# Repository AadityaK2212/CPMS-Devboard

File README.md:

# CPMS-Devboard

That Guy
added to the journal
DESIGN
1h logged
28d ago
Finished! :)
Did the finishing touches, and finished everything In JLCPCB

only issue is that I will need to buy some things seperately and hand soder them because JLCPCB does not have them in stock right now

That Guy
added to the journal
DESIGN
4.5h logged
30d ago
Finishing
I followed the tutorial, and finished it. It took a while, but i fixed my 63 errors, and did all the routing.

When I tried to upload to JLCPCB, the tutorial was not very helpful. I tried everything, and eventually got it through the first stsage. the the BOM. I had no idea how to do it, but after an hour, I installed a plugin, and got it. now, JLCPCB is showing me something weird in the viewer. I posted on slack, and will try to fix it tommorrow.

That Guy
added to the journal
DESIGN
1h logged
Mar 27, 2026
Routing
Nothing much, just a lot of routing, but not done with it. I did have to make a lot of things in the second layer tho.

That Guy
added to the journal
DESIGN
2.5h logged
Mar 25, 2026
Started routing the PCB
Today I started routing the PCB. the first bit went pretty smoothly, but then I started running into problems.

Some of the pins wouldn't connect, and I couldn't figure out why. I tried to figure it out on my own for 20 muinites, but couldn't figure it out. eventually, I asked on slack, and after a 15 minute discussion, I was able to fix it. then, I was able to make the rest of the Flash easily.

I then started on the USB-C. it started fine, untill I realized that two of my pins were swapped for some reason, meaning that I would have to cross the traces to rout them, which would result in a short circut. I thought I was cooked, but then I did ANOTHER 20 muinites of reasearch, and I finally figured it out. except now I had to make multiple layers on my PCB. I fixed it, but I had to move a portion of one of the traces to another layer.

All in a day's work.

That Guy
added to the journal
DESIGN
2.5h logged
Mar 24, 2026
PCB layout
I mostly just started the PCB layout. It took a while and I had to watch a few tutorials, but I got it in the end. not completely done yet though.

The memory was too large, so the tutorial swapped it out for a different version. when I tried that, it wanst in the footprint libraries, so I had to go to SnapMagic and download it. afterwards, I realized they only have the footprint, and not the schematic, so I had to create my own after some more tutorials. I finished the schematic and I am currently wiring it up. will continue on the next session.

That Guy
added to the journal
DESIGN
0.75h logged
Mar 22, 2026
Footprints
I did all the footprints today. There weren't any problems, and I got through it surprisingly easily. also changed the crystal schematic a bit.

That Guy
added to the journal
DESIGN
2.5h logged
Mar 21, 2026
Finished PCB wiring
Finished the PCB design, now I need to make the model.

I finished the USB-C with only onw issue. I didn't know how to chage the capacitors, so I posted my question on slack, and someone answered. other than tht, USB-C went fine.

I did the pinout, which was very repetitive. that alone must have taken over 20 muinites. I didn't have any issues with it.

I did the crystal with only one problem. I didn't know, but KiCad updated one of thier schematic designs, so I asked on slack and fnished it.

That Guy
added to the journal
DESIGN
1h logged
Mar 21, 2026
Starting Devboard
Watched a small tutorial, looked through the tutorial, and started the Devboard.

I started making the devboard, but ran into some minor issues because the schematic of the RP2040 is not the asme as the one in the tutorial. It has the same pins, but in a different order. hopefully won't become an issue :)

Also started on the USB-C connecter, and it's going fine so far.

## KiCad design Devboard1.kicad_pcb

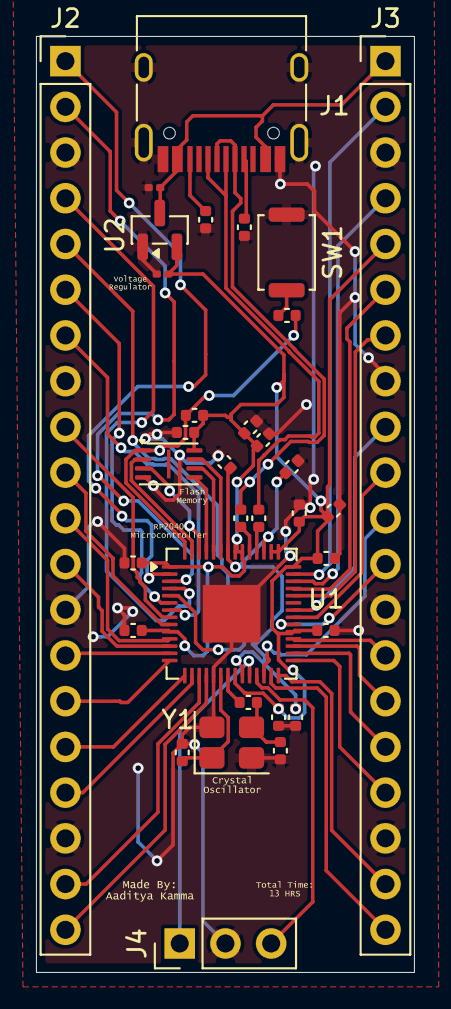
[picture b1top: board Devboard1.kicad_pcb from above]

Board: 2 copper layers, 21.0 x 52.0 mm, 33 parts (0 on the bottom side), 52 nets.

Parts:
C1, C4: 1uF; C_0402_1005Metric
C2, C3, C5, C6, C7, C8, C9, C10, C11, C12, C17: 0.1uF; C_0402_1005Metric
C13, C14: 10uF; C_0201_0603Metric
C15, C16: 33pF; C_0402_1005Metric
J1: USB_C_Receptacle_USB2.0_14P; USB_C_Receptacle_HRO_TYPE-C-31-M-12
J2, J3: Conn_01x20; PinHeader_1x20_P2.54mm_Vertical
J4: Conn_01x03; PinHeader_1x03_P2.54mm_Vertical
R1, R2: 5.1K; C_0402_1005Metric
R3, R4: 27; C_0402_1005Metric
R5, R7: 1K; C_0402_1005Metric
R6: 10K; C_0402_1005Metric
SW1: SW_Push; SW_Push_SPST_NO_Alps_SKRK
U1: RP2040; QFN-56-1EP_7x7mm_P0.4mm_EP3.2x3.2mm
U2: MCP1700x-330xxTT; SOT-23
W25Q16JVZPIQ_TR1: Winbond_USON-8-1EP_3x2mm_P0.5mm_EP0.2x1.6mm
Y1: 12 MHz; Crystal_SMD_3225-4Pin_3.2x2.5mm

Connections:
+1V1: C1.1, C2.1, C3.1, U1.23 (DVDD), U1.45 (VREG_VOUT), U1.50 (DVDD)
+3V3: C4.1, C5.1, C6.1, C7.1, C8.1, C9.1, C10.1, C11.1, C12.1, C14.1, C17.1, J3.5, R6.1, U1.1 (IOVDD), U1.10 (IOVDD), U1.22 (IOVDD), U1.33 (IOVDD), U1.42 (IOVDD), U1.43 (ADC_AVDD), U1.44 (VREG_VIN), U1.48 (USB_VDD), U1.49 (IOVDD), U2.2 (VO), W25Q16JVZPIQ_TR1.8 (VCC)
GND: C1.2, C2.2, C3.2, C4.2, C5.2, C6.2, C7.2, C8.2, C9.2, C10.2, C11.2, C12.2, C13.2, C14.2, C15.1, C16.1, C17.2, J1.A1 (GND), J1.A12 (GND), J1.B1 (GND), J1.B12 (GND), J1.S1 (SHIELD), J2.3, J2.8, J2.13, J2.18, J3.3, J3.8, J3.13, J3.18, J4.2, R1.2, R2.2, SW1.1, U1.19 (TESTEN), U1.57 (GND), U2.1 (GND), W25Q16JVZPIQ_TR1.4 (GND), Y1.2 (G), Y1.4 (G)
GPIO0: J2.1, U1.2 (GPIO0)
GPIO1: J2.2, U1.3 (GPIO1)
GPIO2: J2.4, U1.4 (GPIO2)
GPIO3: J2.5, U1.5 (GPIO3)
GPIO4: J2.6, U1.6 (GPIO4)
GPIO5: J2.7, U1.7 (GPIO5)
GPIO6: J2.9, U1.8 (GPIO6)
GPIO7: J2.10, U1.9 (GPIO7)
GPIO8: J2.11, U1.11 (GPIO8)
GPIO9: J2.12, U1.12 (GPIO9)
GPIO10: J2.14, U1.13 (GPIO10)
GPIO11: J2.15, U1.14 (GPIO11)
GPIO12: J2.16, U1.15 (GPIO12)
GPIO13: J2.17, U1.16 (GPIO13)
GPIO14: J2.19, U1.17 (GPIO14)
GPIO15: J2.20, U1.18 (GPIO15)
GPIO16: J3.20, U1.27 (GPIO16)
GPIO17: J3.19, U1.28 (GPIO17)
GPIO18: J3.17, U1.29 (GPIO18)
GPIO19: J3.16, U1.30 (GPIO19)
GPIO20: J3.15, U1.31 (GPIO20)
GPIO21: J3.14, U1.32 (GPIO21)
GPIO22: J3.12, U1.34 (GPIO22)
GPIO23: J3.10, U1.35 (GPIO23)
GPIO24: J3.9, U1.36 (GPIO24)
GPIO26_ADC0: J3.7, U1.38 (GPIO26/ADC0)
GPIO27_ADC1: J3.6, U1.39 (GPIO27/ADC1)
GPIO28_ADC2: J3.4, U1.40 (GPIO28/ADC2)
GPIO29_ADC3: J3.2, U1.41 (GPIO29/ADC3)
unnamed: C15.2, R5.1, Y1.3
unnamed: J1.A5 (CC1), R2.1
unnamed: J1.B5 (CC2), R1.1
unnamed: R7.1, SW1.2
unnamed: R3.2, U1.46 (USB_DM)
unnamed: R4.2, U1.47 (USB_DP)
QSPI_SCLK: U1.51 (QSPI_SD3), W25Q16JVZPIQ_TR1.7 (/HOLD/IO3)
QSPI_SD0: U1.52 (QSPI_SCLK), W25Q16JVZPIQ_TR1.6 (CLK)
QSPI_SD1: U1.53 (QSPI_SD0), W25Q16JVZPIQ_TR1.5 (DI/IO0)
QSPI_SD2: U1.55 (QSPI_SD1), W25Q16JVZPIQ_TR1.2 (DO/IO1)
QSPI_SD3: U1.54 (QSPI_SD2), W25Q16JVZPIQ_TR1.3 (/WP/IO2)
QSPI_SS: R6.2, R7.2, U1.56 (~QSPI_SS), W25Q16JVZPIQ_TR1.1 (/CS)
RUN: J3.11, U1.26 (RUN)
SWCLK: J4.1, U1.24 (SWCLK)
SWD: J4.3, U1.25 (SWDIO)
USB_D+: J1.A7 (D-), J1.B7 (D-), R4.1
USB_D-: J1.A6 (D+), J1.B6 (D+), R3.1
VBUS: C13.1, J1.A4 (VBUS), J1.A9 (VBUS), J1.B4 (VBUS), J1.B9 (VBUS), J3.1, U2.3 (VI)
XIN: C16.2, U1.20 (XIN), Y1.1
XOUT: R5.2, U1.21 (XOUT)

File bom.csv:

Designator,Footprint,Quantity,Value,LCSC Part #
"C1, C4",0402,2,1uF,
"C10, C11, C12, C17, C2, C3, C5, C6, C7, C8, C9",0402,11,0.1uF,
"C13, C14",0201,2,10uF,
"C15, C16",0402,2,33pF,
J1,USB_C_Receptacle_HRO_TYPE-C-31-M-12,1,USB_C_Receptacle_USB2.0_14P,
"J2, J3",PinHeader_1x20_P2.54mm_Vertical,2,Conn_01x20,
J4,PinHeader_1x03_P2.54mm_Vertical,1,Conn_01x03,
"R1, R2",0402,2,5.1K,
"R3, R4",0402,2,27,
"R5, R7",0402,2,1K,
R6,0402,1,10K,
SW1,SW_Push_SPST_NO_Alps_SKRK,1,SW_Push,
U1,QFN-56-1EP_7x7mm_P0.4mm_EP3.2x3.2mm,1,RP2040,
U2,SOT-23,1,MCP1700x-330xxTT,
W25Q16JVZPIQ_TR1,Winbond_USON-8-1EP_3x2mm_P0.5mm_EP0.2x1.6mm,1,~,
Y1,Crystal_SMD_3225-4Pin_3.2x2.5mm,1,12 MHz,

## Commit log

2026-04-29 Update README with design journal entries
    Added detailed journal entries documenting the design process, including time logged and issues encountered while working on the PCB layout, routing, and component footprints.
2026-04-29 Add image to README
    Added an image to the README for visual context.
2026-05-13 Add images to README for enhanced visuals
    Added two new images to the README for better visualization.
